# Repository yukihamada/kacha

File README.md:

# KAGI — スマートホーム管理

> 鍵・照明・民泊をまとめて管理。E2E暗号化で安全にシェア。

## Features

- **スマートロック** — SwitchBot, Sesame, Nuki, Qrio対応
- **照明制御** — Philips Hue シーン管理
- **Beds24予約同期** — Airbnb/Booking.com予約を自動取得
- **E2E暗号化シェア** — AES-256-GCM、サーバーに平文保存なし
- **チーム管理** — ゲスト/清掃/マネージャー/オーナー代理の4段階
- **複数物件** — スワイプで切り替え、総合ダッシュボード
- **収支レポート** — 月別グラフ、プラットフォーム別内訳
- **バックグラウンド通知** — 新規予約をプッシュ通知
- **オートロック解除** — SwitchBot Botでインターホン遠隔解除
- **ジオフェンス** — 自宅に近づいたら通知

## Architecture

```
iOS (SwiftUI + SwiftData)
├── Local-first — 全データは端末に保存
├── E2E Encryption — CryptoKit AES-256-GCM
├── Keychain Backup — 再インストール後も復元
└── Background Fetch — BGAppRefreshTask

Server (Rust + axum + SQLite)
├── kacha-server.fly.dev / kacha.pasha.run
├── 暗号化blobのみ保存
├── Universal Links (AASA)
└── 期限管理 + 取り消しAPI
```

## Tech Stack

| Layer | Technology |
|-------|-----------|
| iOS | SwiftUI, SwiftData, CryptoKit, CoreLocation, Charts |
| Server | Rust, axum 0.7, SQLite (rusqlite), Fly.io |
| Smart Home | SwitchBot API, Sesame API, Philips Hue, Nuki Web API |
| PMS | Beds24 API v2 |
| Security | AES-256-GCM E2E, Keychain, URL fragment key |

## Getting Started

```bash
# Clone
git clone https://github.com/yukihamada/kacha.git
cd kacha/ios

# Generate Xcode project
xcodegen generate

# Build & run on simulator
xcodebuild -project Kacha.xcodeproj -scheme Kacha \
  -destination 'platform=iOS Simulator,name=iPhone 16 Pro' build

# Run tests
xcodebuild test -project Kacha.xcodeproj -scheme Kacha \
  -destination 'platform=iOS Simulator,name=iPhone 16 Pro' \
  -only-testing:KachaTests
```

## Server

```bash
cd server
cargo run  # localhost:8080
# Deploy
fly deploy --remote-only -a kacha-server
```

## Contributing

PRs welcome! See [CONTRIBUTING.md](CONTRIBUTING.md) for guidelines.

1. Fork the repo
2. Create a feature branch
3. Make your changes
4. Run tests
5. Submit a PR

## License

MIT

## Links

- [TestFlight Beta](https://testflight.apple.com/join/tntB2b27)
- [kacha.pasha.run](https://kacha.pasha.run) — Universal Links + Privacy + Support
- [enablerdao.com](https://enablerdao.com) — Enabler vision
- [Beds24 API](https://beds24.com/api/v2) — PMS integration docs

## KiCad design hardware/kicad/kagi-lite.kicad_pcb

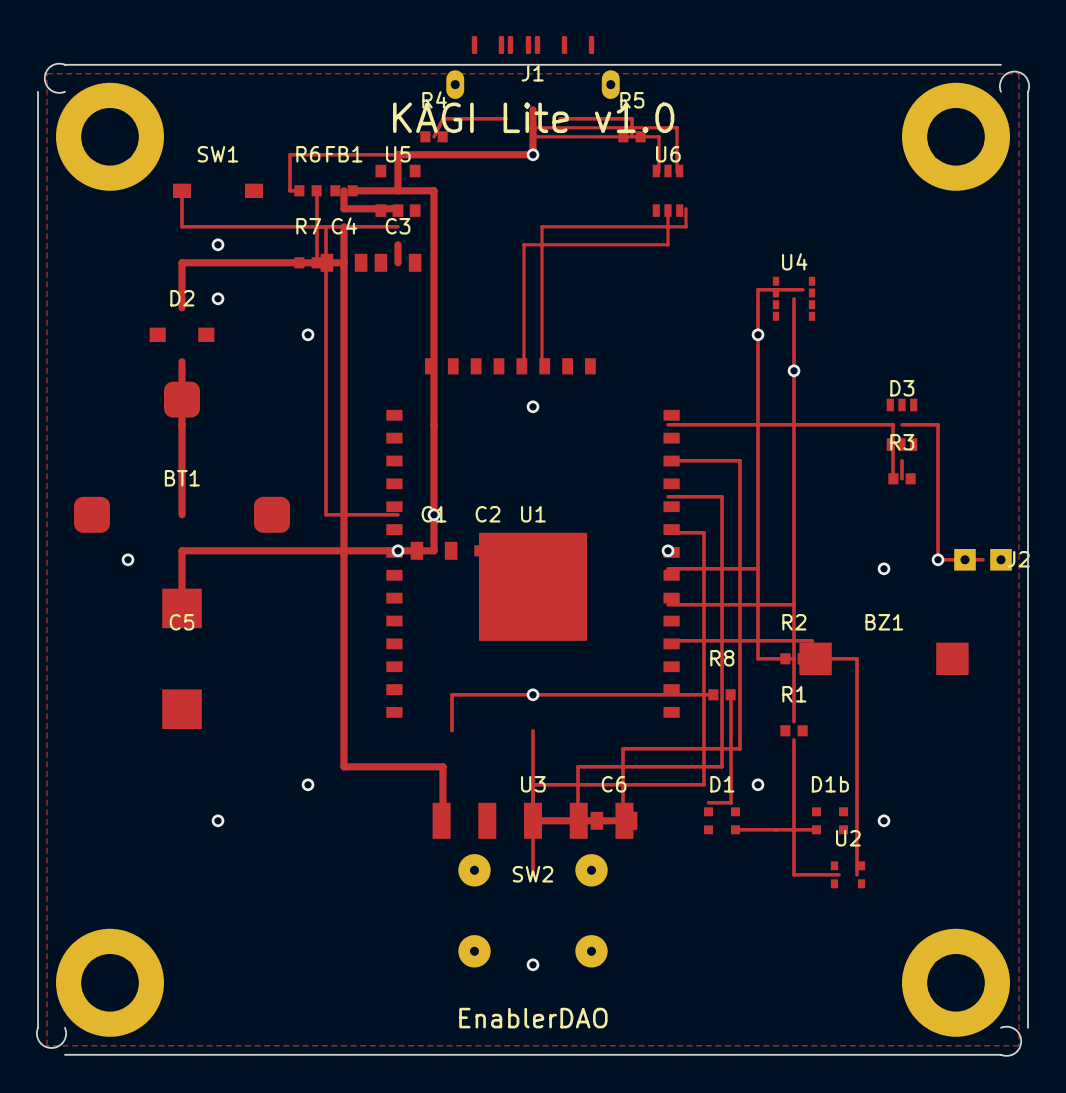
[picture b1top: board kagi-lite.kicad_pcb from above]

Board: 4 copper layers, 55.1 x 55.1 mm, 31 parts (0 on the bottom side), 21 nets.

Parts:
BT1: CR2032; BT1
BZ1: MLT-8530; BZ1
C1: 10uF; C1
C2: 100nF; C2
C3: 22uF; C3
C4: 22uF; C4
C5: 470uF; C5
C6: 10uF; C6
D1: WS2812B; D1
D1b: WS2812B; D1b
D2: 1N5819W; D2
D3: PRTR5V0U2X; D3
FB1: BLM18PG601; FB1
J1: USB-C; J1
J2: JST-PH-2P; J2
R1: 4.7K; R1
R2: 4.7K; R2
R3: 10K; R3
R4: 5.1K; R4
R5: 5.1K; R5
R6: 100K; R6
R7: 100K; R7
R8: 33R; R8
SW1: Reset; SW1
SW2: I'm OK Button; SW2
U1: ESP32-S3-MINI-1-N8; U1
U2: SHT40-AD1B-R2; U2
U3: LD2410B; U3
U4: ATECC608A; U4
U5: RT9013-33GB; U5
U6: USBLC6-2SC6; U6

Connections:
+3V3: C1.1, C2.1, C5.1, D1.1, D1b.1, D2.2, D3.5, FB1.2, R1.2, R2.2, R3.2, U1.2, U2.4, U4.7, U4.8
+5V: C4.1, C6.1, J1.A4, J1.A9, J1.B4, J1.B9, R6.1, U3.1, U5.1, U5.3, U6.5
CC1: J1.A5, R4.1
CC2: J1.B5, R5.1
EN: SW1.1, U1.3
GND: BT1.2, BT1.3, BZ1.2, C1.2, C2.2, C3.2, C4.2, C5.2, C6.2, D1.3, D1b.3, D3.2, J1.A1, J1.A12, J1.B1, J1.B12, J1.S1, J1.S2, J2.2, R4.2, R5.2, R7.2, SW1.2, SW2.3, SW2.4, U1.1, U1.36, U1.37, U2.2, U3.2, U4.4, U5.2, U6.2
GPIO2_BTN: SW2.1, SW2.2, U1.34
GPIO3_DOOR: D3.1, D3.3, J2.1, R3.1
GPIO4_RADAR: U1.4, U3.5
GPIO14_TX: U1.20, U3.3
GPIO15_RX: U1.8, U3.4
GPIO17_BZ: BZ1.1, U1.10
LDO_OUT: C3.1, FB1.1, U5.5
SCL: R2.1, U1.15, U2.3, U4.6
SDA: R1.1, U1.12, U2.1, U4.5
USB_DM: J1.A7, J1.B6, U6.1, U6.6
USB_DP: J1.A6, J1.B7, U6.3, U6.4
VBAT: BT1.1, D2.1
VBUS_MID: R6.2, R7.1
WS_CHAIN: D1.2, D1b.4
WS_R8: D1.4, R8.2, U1.29

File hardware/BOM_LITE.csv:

Reference,Value,Package,Manufacturer,MPN,Description,Quantity,Unit Price (USD),Source,Mission Role
U1,ESP32-S3-MINI-1-N8,ESP32-S3-MINI,Espressif,ESP32-S3-MINI-1-N8,WiFi+BLE5.0 MCU 8MB Flash 技適認証済(201-220017),1,3.20,LCSC (C2913206),通知送信・アルゴリズム実行
U2,SHT40-AD1B-R2,DFN-4 (1.5x1.5mm),Sensirion,SHT40-AD1B-R2,Temperature & Humidity Sensor ±0.2°C ±1.8%RH I2C 0x44,1,2.20,Digi-Key,体調悪化・熱中症検知 (極端な温湿度)
U3,LD2410B,SMD Module (35x7mm),Hi-Link,LD2410B,60GHz mmWave Radar Presence+Breathing Sensor UART+OUT 5V,1,2.00,AliExpress/LCSC,呼吸・在室検知 ← コア機能
U4,ATECC608A-MAHDA-T,UDFN-8 (2x3mm),Microchip,ATECC608A-MAHDA-T,Secure Element I2C 0x60 ECC P-256 — 安否ログ署名・改ざん防止,1,0.60,Digi-Key,監査ログの法的証跡
U5,RT9013-33GB,SOT-23-5,Richtek,RT9013-33GB,3.3V LDO 500mA SOT-23-5 Iq=55uA,1,0.05,LCSC (C145239),安定電源
U6,USBLC6-2SC6,SOT-23-6,STMicroelectronics,USBLC6-2SC6,USB ESD Protection Diode,1,0.25,LCSC (C7519),耐久性
J1,USB-C Receptacle,USB-C SMD 16pin,Korean Hroparts Elec,TYPE-C-31-M-12,USB Type-C Connector 16Pin SMD,1,0.30,LCSC (C165948),電源
J2,JST PH 2Pin,JST PH 2.0mm,JST,B2B-PH-K-S(LF)(SN),Door Sensor Cable Connector (MC-38),1,0.08,LCSC (C131337),ドア開閉検知
BT1,CR2032 Holder,SMD Battery Holder,Linx Technologies,BAT-HLD-001-SMT,CR2032 SMD Battery Holder (停電時BLE緊急通知),1,0.60,LCSC (C75811),停電でも動く
SW1,Tactile Switch,SMD 3x4x2mm,C&K,PTS636 SM25F SMTR LFS,Reset Button → EN Pin,1,0.10,LCSC (C2837610),工場リセット
SW2,Tactile Switch 12mm,SMD 12x12x4.3mm,C&K,PTS125 SM43 SMTR2 LFS,"I'm OK ボタン (GPIO2) — 最重要UI。1日1回押すと家族に通知 / 未押3日→Tier2",1,0.15,LCSC,★ 生存確認の最後の砦 ★
D1,WS2812B-2020,2020 (2.0x2.0mm),Worldsemi,WS2812B-2020,RGB LED (緑=正常 / 赤=異常 / 黄=確認待ち / 青=通信中),1,0.08,LCSC (C965555),一目で状態確認
D2,1N5819W,SOD-123,MDD,1N5819W,Schottky Diode 40V 1A (CR2032 ORing),1,0.03,LCSC (C191023),停電対策
D3,PRTR5V0U2X,SOT-363,Nexperia,PRTR5V0U2X,TVS Diode ESD Protection — Door Sensor GPIO3,1,0.10,LCSC (C2827654),外部ケーブル保護
R1,4.7K,0402,Yageo,RC0402JR-074K7L,I2C SDA Pull-up,1,0.002,LCSC (C25900),
R2,4.7K,0402,Yageo,RC0402JR-074K7L,I2C SCL Pull-up,1,0.002,LCSC (C25900),
R3,10K,0402,Yageo,RC0402JR-0710KL,Pull-up for Door Sensor GPIO3,1,0.002,LCSC (C25744),
R4,5.1K,0402,Yageo,RC0402JR-075K1L,USB-C CC1,1,0.002,LCSC (C25905),
R5,5.1K,0402,Yageo,RC0402JR-075K1L,USB-C CC2,1,0.002,LCSC (C25905),
R6,100K,0402,Yageo,RC0402JR-07100KL,VBUS Voltage Divider High (停電検知),1,0.002,LCSC (C25741),停電検知
R7,100K,0402,Yageo,RC0402JR-07100KL,VBUS Voltage Divider Low,1,0.002,LCSC (C25741),
R8,33,0402,Yageo,RC0402JR-0733RL,WS2812B Data Series Resistor,1,0.002,LCSC (C25900),
C1,10uF,0805,Samsung,CL21A106KAYNNNE,ESP32-S3 VDD3P3 Bypass Cap,2,0.02,LCSC (C15850),
C2,100nF,0402,Samsung,CL05B104KO5NNNC,IC Decoupling Cap (x6: U2/U3/U4/U5/U6/EN),6,0.005,LCSC (C1525),
C3,22uF,0805,Samsung,CL21A226MAQNNNE,LDO 3.3V Output Bypass,1,0.03,LCSC (C45783),
C4,22uF,0805,Samsung,CL21A226MAQNNNE,LDO 5V Input Bypass,1,0.03,LCSC (C45783),
C5,470uF 6.3V,SMD 6.3x7.7mm,Nichicon,UWT1C471MNL1GS,CR2032 Backup Burst Current Buffer,1,0.12,LCSC (C330803),停電対策
C6,10uF,0805,Samsung,CL21A106KAYNNNE,LD2410B 5V Bulk Bypass Cap,1,0.02,LCSC (C15850),
FB1,600R@100MHz,0402,Murata,BLM18PG601SN1D,Ferrite Bead EMI Filter,1,0.05,LCSC (C1015),
BZ1,Active Piezo Buzzer 3V,SMD 9x6mm,Jiangsu Huaneng,MLT-8530,Active Buzzer — Tier1ブザー・I'm OK確認音,1,0.10,LCSC (C96044),本人への気づき促し
TP1,Test Point 3.3V,1mm pad,-,-,Factory Test Point,1,0,LCSC,
TP2,Test Point GND,1mm pad,-,-,Factory Test Point,1,0,LCSC,
TP3,Test Point GPIO0,1mm pad,-,-,BOOT pin — Flash専用,1,0,LCSC,
DOOR1,MC-38,Wired Reed Switch,Generic,MC-38,Door/Window Magnetic Reed Switch,1,1.20,AliExpress,ドア48時間未開=生存確認アラート

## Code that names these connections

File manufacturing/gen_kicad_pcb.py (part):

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    3: '"+5V"',
    4: '"SDA"',
    5: '"SCL"',
    6: '"GPIO2_BTN"',
    7: '"GPIO3_DOOR"',
    8: '"GPIO4_RADAR"',
    9: '"GPIO14_TX"',
    10: '"GPIO15_RX"',
    11: '"GPIO17_BZ"',
    12: '"GPIO38_LED"',
    13: '"GPIO1_ADC"',
    14: '"USB_DP"',
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        'IO38': 20,  # GPIO38 → WS2812_DATA (through R8)
    }
    # USB is handled via USBLC6
    esp_nets['IO19'] = 15  # USB_DM (through U6)
    esp_nets['IO20'] = 14  # USB_DP (through U6)

    c = COMPS
    parts.append(gen_footprint('U1', c['U1'][3], *c['U1'][:3], pads_esp32s3(esp_nets)))
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    ld_pads = [
        (1, 'smd', 'rect', -5.08, 0, 1.0, 2.0, F_Cu, 3),   # VCC=5V
        (2, 'smd', 'rect', -2.54, 0, 1.0, 2.0, F_Cu, 1),   # GND
        (3, 'smd', 'rect',  0,    0, 1.0, 2.0, F_Cu, 9),   # RX←GPIO14_TX
        (4, 'smd', 'rect',  2.54, 0, 1.0, 2.0, F_Cu, 10),  # TX→GPIO15_RX
        (5, 'smd', 'rect',  5.08, 0, 1.0, 2.0, F_Cu, 8),   # OUT→GPIO4
    ]
    parts.append(gen_footprint('U3', c['U3'][3], *c['U3'][:3], ld_pads))
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    traces.append(seg(40.0, 42.5, 42.5, 42.5, TW, F_Cu, 5))  # → U4 SCL

    # ── UART to LD2410B ──
    # GPIO14_TX → U3 pin3(RX)
    traces.append(seg(35.0, 29.0, 37.0, 29.0, TW, F_Cu, 9))
    traces.append(seg(37.0, 29.0, 37.0, 15.0, TW, F_Cu, 9))
    traces.append(seg(37.0, 15.0, 27.5, 15.0, TW, F_Cu, 9))
    traces.append(seg(27.5, 15.0, 27.5, 13.0, TW, F_Cu, 9))

    # GPIO15_RX ← U3 pin4(TX)
    traces.append(seg(35.0, 31.0, 38.0, 31.0, TW, F_Cu, 10))
    traces.append(seg(38.0, 31.0, 38.0, 16.0, TW, F_Cu, 10))
    traces.append(seg(38.0, 16.0, 30.0, 16.0, TW, F_Cu, 10))
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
